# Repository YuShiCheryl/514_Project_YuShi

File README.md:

**Presentation Slides**

**Process Photos**

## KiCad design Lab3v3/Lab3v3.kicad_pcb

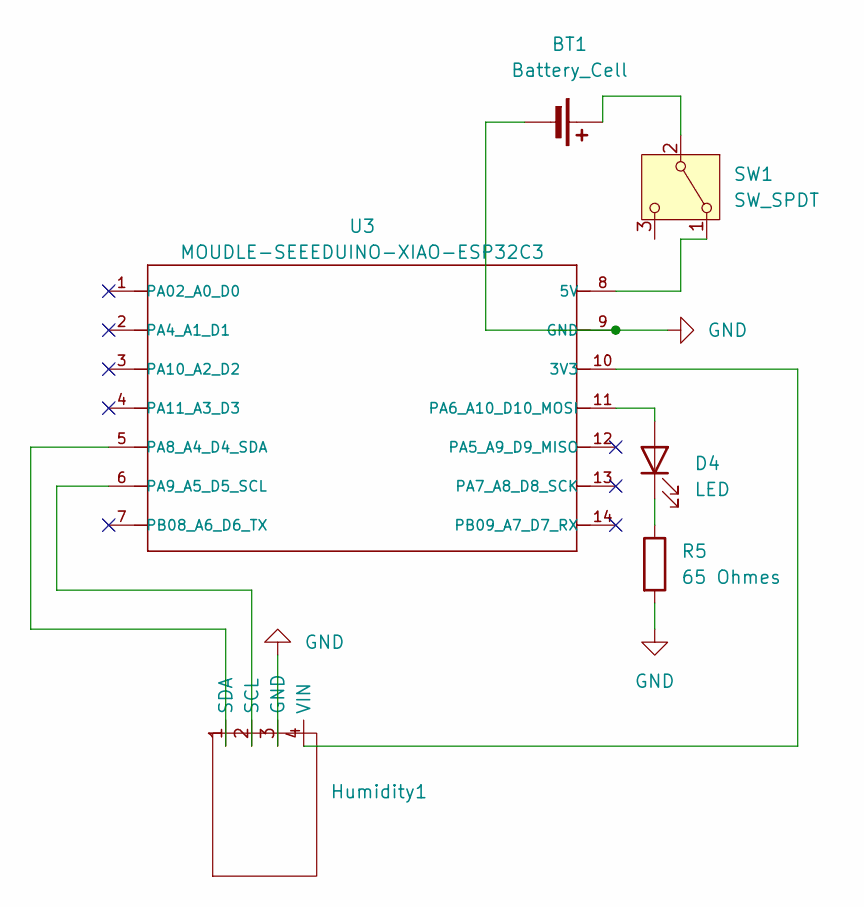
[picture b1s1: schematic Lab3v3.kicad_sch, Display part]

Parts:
BT1: Battery_Cell; JST_PH_B2B-PH-K_1x02_P2.00mm_Vertical
D4: LED; LED_D5.0mm
Humidity1: 128x64OLED
R5: 65 Ohmes; R_Axial_DIN0207_L6.3mm_D2.5mm_P10.16mm_Horizontal
SW1: SW_SPDT; PinHeader_1x03_P2.54mm_Vertical
U3: MOUDLE-SEEEDUINO-XIAO-ESP32C3; XIAO_ESP32_SENSE

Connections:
GND: BT1.2 (-), Humidity1.3 (GND), R5.2, U3.9 (GND)
unnamed: BT1.1 (+), SW1.2 (B)
unnamed: D4.2 (A), U3.11 (PA6_A10_D10_MOSI)
unnamed: D4.1 (K), R5.1
unnamed: Humidity1.2 (SCL), U3.6 (PA9_A5_D5_SCL)
unnamed: Humidity1.1 (SDA), U3.5 (PA8_A4_D4_SDA)
unnamed: Humidity1.4 (VIN), U3.10 (3V3)
unnamed: SW1.1 (A), U3.8 (5V)

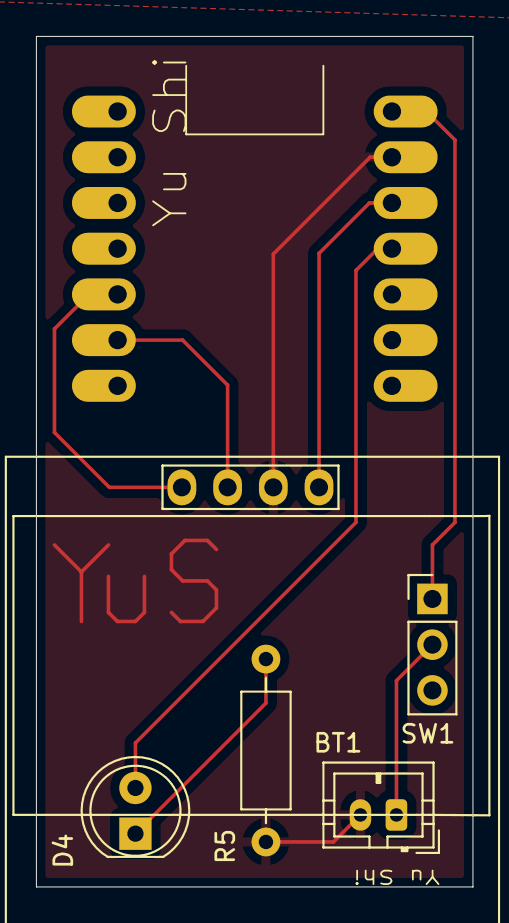
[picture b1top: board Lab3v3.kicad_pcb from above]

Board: 2 copper layers, 24.2 x 47.2 mm, 6 parts (0 on the bottom side), 8 nets.

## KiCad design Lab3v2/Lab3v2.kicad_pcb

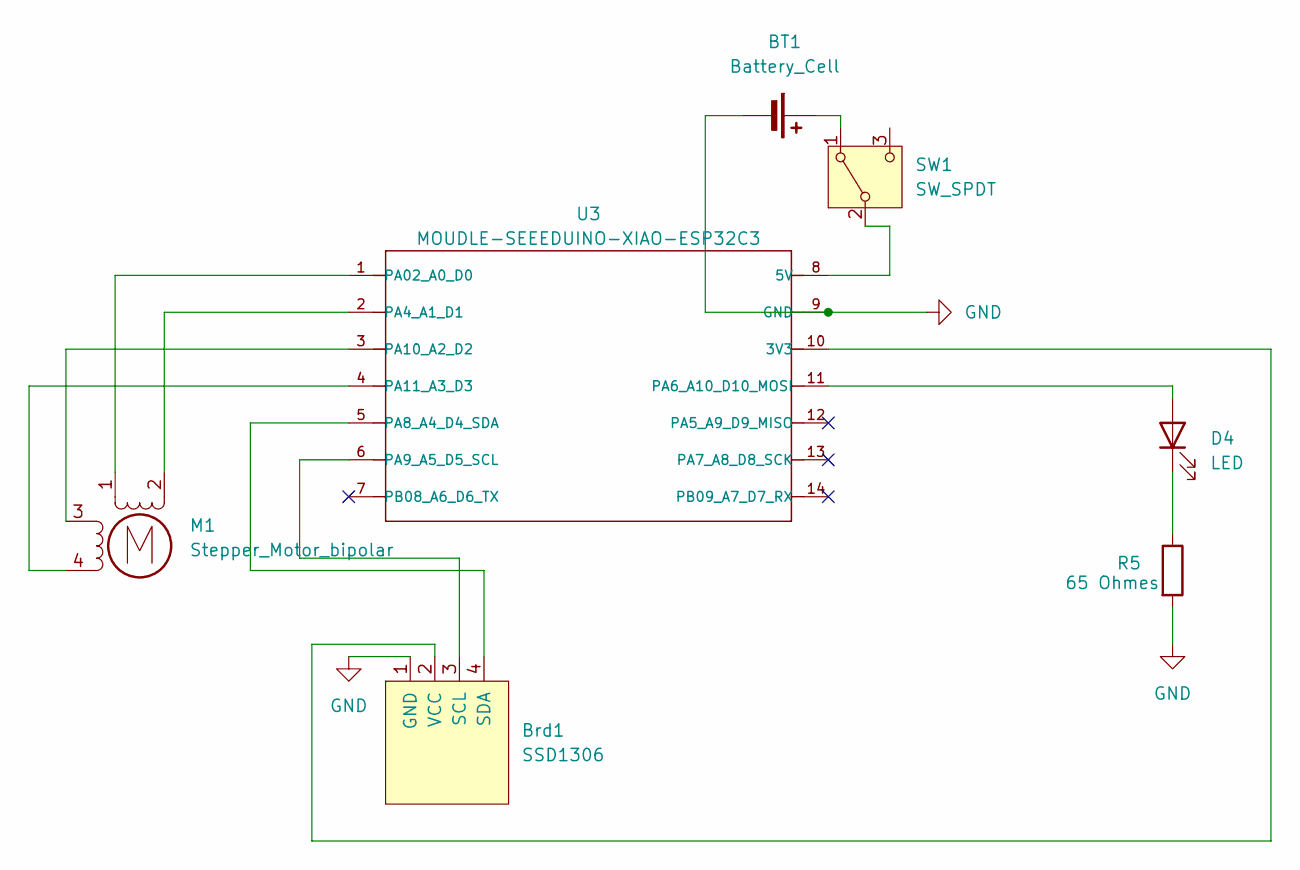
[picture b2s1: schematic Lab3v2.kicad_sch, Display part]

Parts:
BT1: Battery_Cell; JST_PH_B2B-PH-K_1x02_P2.00mm_Vertical
Brd1: SSD1306; 128x64OLED
D4: LED; LED_D5.0mm
M1: Stepper_Motor_bipolar; x27_stepper
R5: 65 Ohmes; R_Axial_DIN0207_L6.3mm_D2.5mm_P10.16mm_Horizontal
SW1: SW_SPDT; PinHeader_1x03_P2.54mm_Vertical
U3: MOUDLE-SEEEDUINO-XIAO-ESP32C3; XIAO_ESP32_SENSE

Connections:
GND: BT1.2 (-), Brd1.1 (GND), R5.2, U3.9 (GND)
unnamed: BT1.1 (+), SW1.1 (A)
unnamed: Brd1.3 (SCL), U3.6 (PA9_A5_D5_SCL)
unnamed: Brd1.4 (SDA), U3.5 (PA8_A4_D4_SDA)
unnamed: Brd1.2 (VCC), U3.10 (3V3)
unnamed: D4.2 (A), U3.11 (PA6_A10_D10_MOSI)
unnamed: D4.1 (K), R5.1
unnamed: M1.2 (-), U3.2 (PA4_A1_D1)
unnamed: SW1.2 (B), U3.8 (5V)
unnamed: M1.1, U3.1 (PA02_A0_D0)
unnamed: M1.3, U3.3 (PA10_A2_D2)
unnamed: M1.4, U3.4 (PA11_A3_D3)

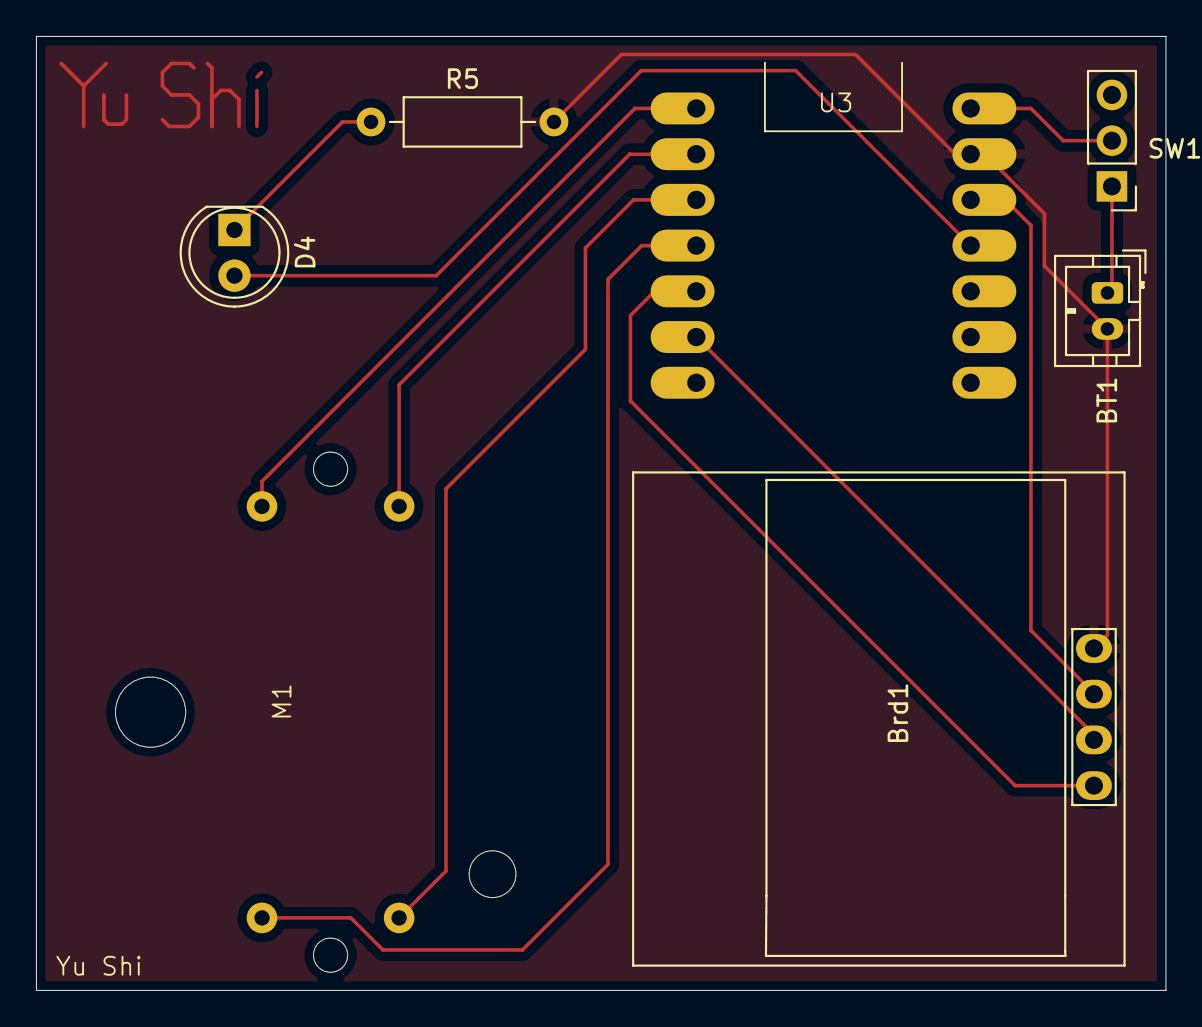
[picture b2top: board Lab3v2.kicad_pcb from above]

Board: 2 copper layers, 62.8 x 53.0 mm, 7 parts (0 on the bottom side), 12 nets.

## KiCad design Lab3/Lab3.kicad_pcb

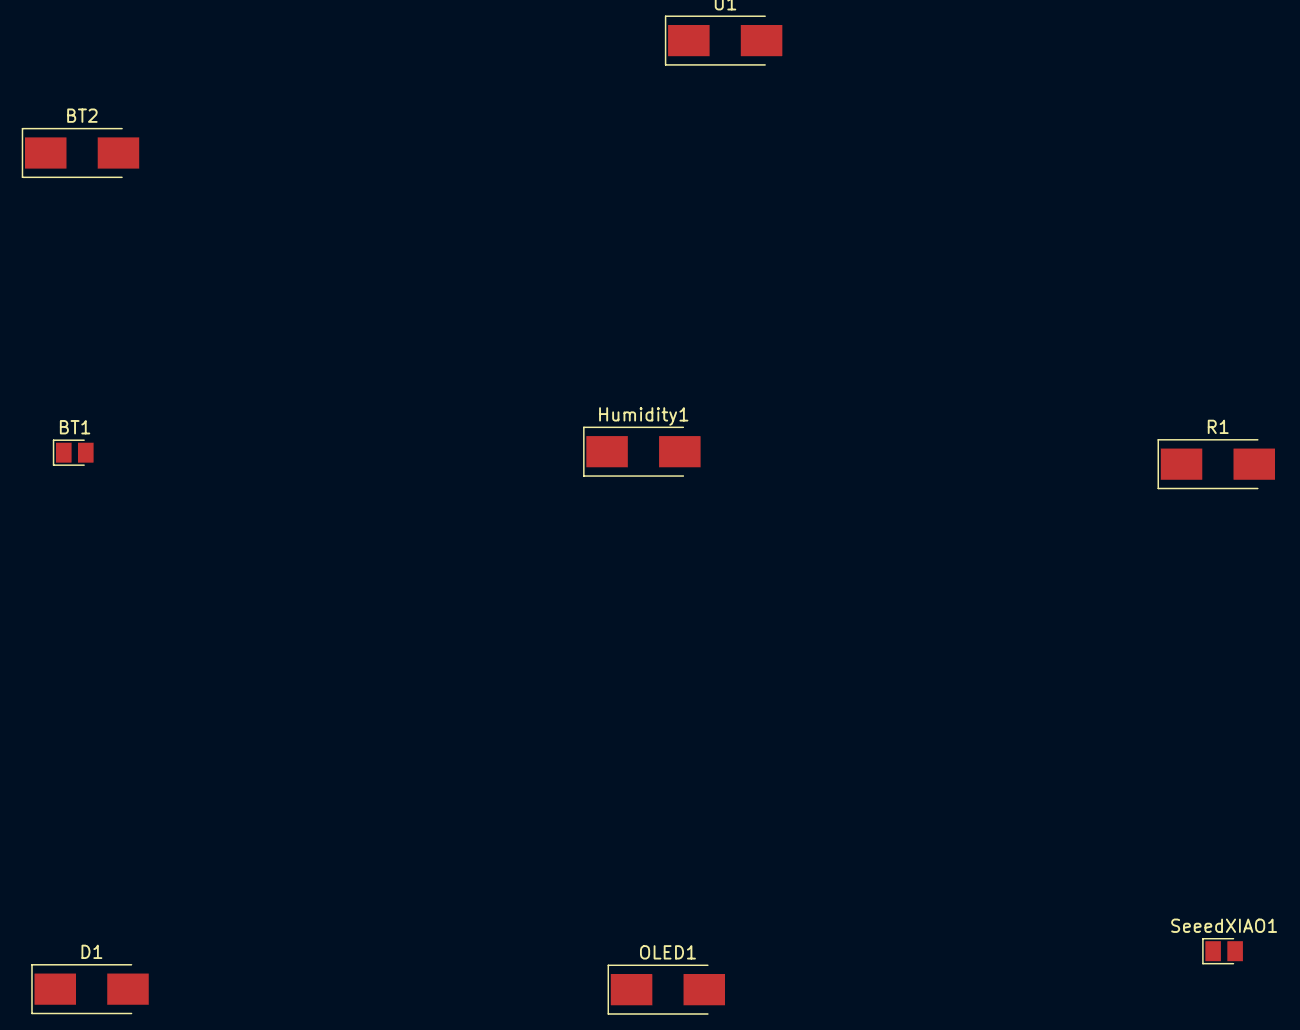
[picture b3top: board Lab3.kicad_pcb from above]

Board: 2 copper layers, 8 parts (0 on the bottom side), 3 nets, no tracks yet.

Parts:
BT1: Battery_Cell; LED_Cree-XQ_HandSoldering
BT2: Battery_Cell; Crystal_SMD_0603-2Pin_6.0x3.5mm_HandSoldering
D1: LED; Crystal_SMD_0603-2Pin_6.0x3.5mm_HandSoldering
Humidity1: Crystal_SMD_0603-2Pin_6.0x3.5mm_HandSoldering
OLED1: Crystal_SMD_0603-2Pin_6.0x3.5mm_HandSoldering
R1: R; Crystal_SMD_0603-2Pin_6.0x3.5mm_HandSoldering
SeeedXIAO1: LED_Cree-XQ_HandSoldering
U1: MOUDLE-SEEEDUINO-XIAO-ESP32C3; Crystal_SMD_0603-2Pin_6.0x3.5mm_HandSoldering

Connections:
unnamed: BT2.2 (-), R1.2
unnamed: D1.2 (A), U1.1 (PA02_A0_D0)
unnamed: D1.1 (K), R1.1

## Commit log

2025-03-10 Create Test
